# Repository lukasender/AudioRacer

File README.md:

AudioRacer
=========
University Project

### Videos

[YouTube: Wireless car control via zigbee](http://www.youtube.com/watch?v=whj3E_e5Ng8) (First test run)

[YouTube: AudioRacer](http://www.youtube.com/watch?v=RgHPVbPUozI)

### Information
C code for the ZigBee control software is not hosted on github due to the Texas Instruments Inc. Library license model.

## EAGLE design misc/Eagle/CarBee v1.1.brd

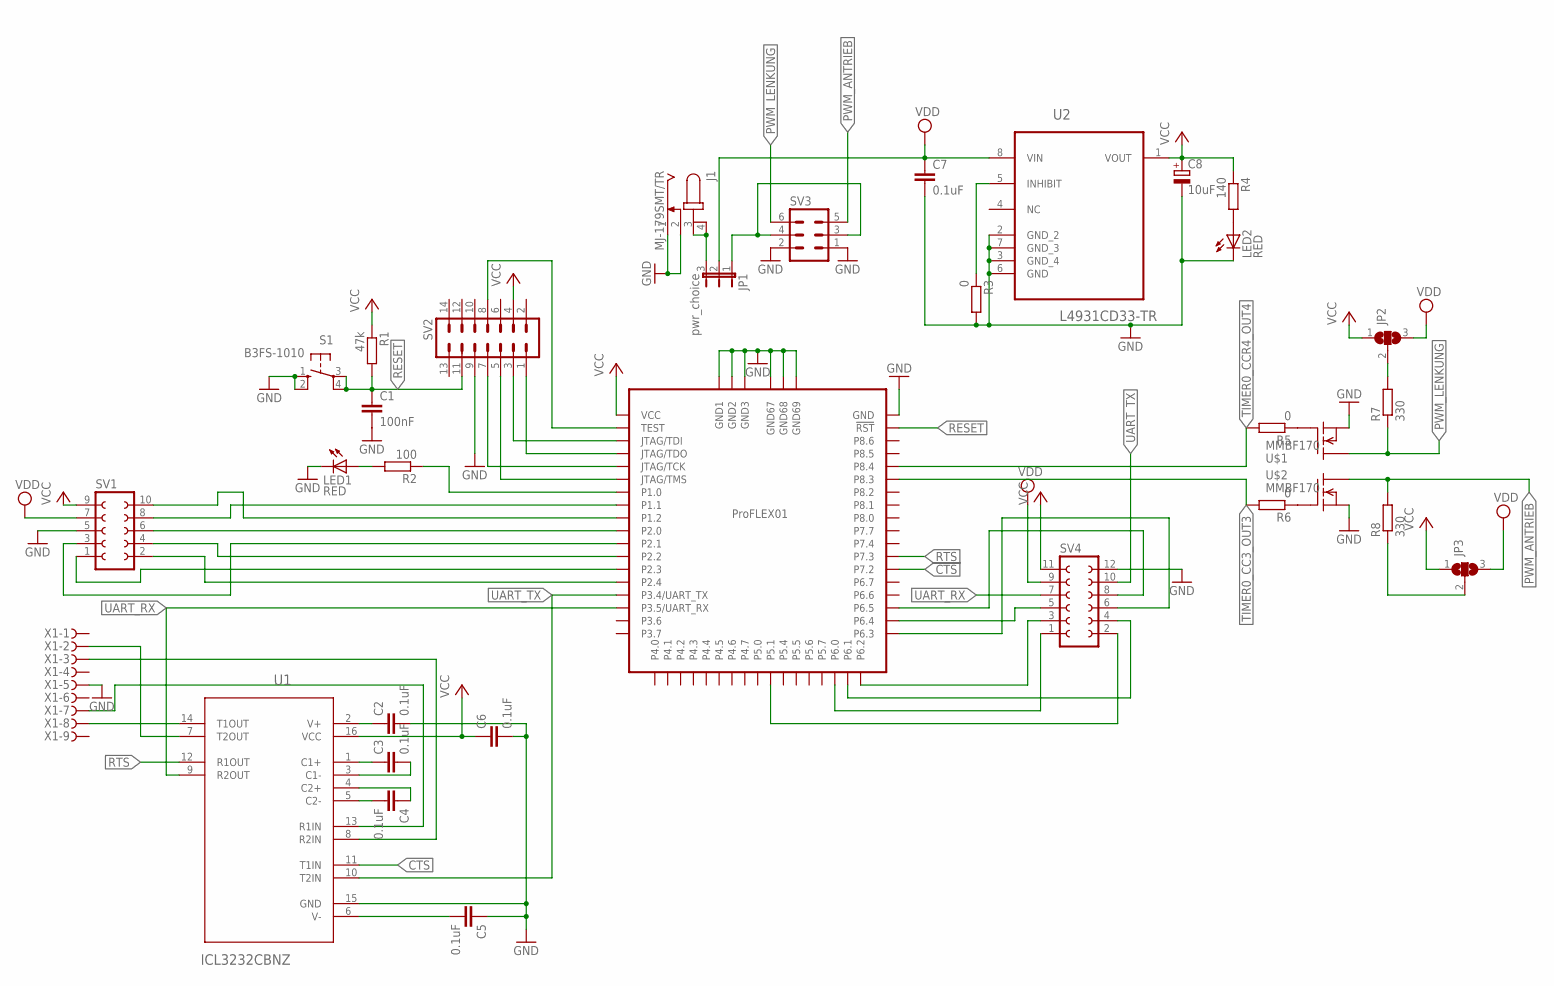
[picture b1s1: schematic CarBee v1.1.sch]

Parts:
C1: 100nF; C0603; MPN 0306ZC104KAT2A
C2, C4, C5, C7: 0.1uF; C0603
C3, C6: 0.1uF; C0603; MPN 0306ZC104KAT2A
C8: 10uF; PANASONIC_B
J1: MJ-179SMT/TR; MJ-179SMT
JP1: pwr_choice; JP2
JP2, JP3: SJ2W; SJ_2
LED1, LED2: RED; CHIP-LED0603
MOD1: PROFLEX01; MODFLEX01
R1: 47k; R0603
R2: 100; R0603
R3, R5, R6: 0; R0603
R4: 140; R0603
R7, R8: 330; R0603
S1: B3FS-1010
SV1: FE05-2
SV2: ML14
SV3: MA03-2
SV4: FE06-2
U1: ICL3232CBNZ; SOIC127P600X175-16N
U2: L4931CD33-TR; SOIC127P600X175-8N
U$1, U$2: MMBF170; SOT23
X1: F09HPS; F09HP

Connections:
CTS: MOD1.P$37 (P7.2), U1.11 (T1IN)
GND: C1.2, C2.2, C5.1, C6.2, C7.2, C8.-, J1.1, J1.2, LED1.C, LED2.C, MOD1.P$1 (GND1), MOD1.P$2 (GND2), MOD1.P$3 (GND3), MOD1.P$44 (GND), MOD1.P$67 (GND67), MOD1.P$68 (GND68), MOD1.P$69 (GND69), R3.2, S1.1 (S), S1.2 (S1), SV1.5, SV2.9, SV3.1, SV3.2, SV4.12, U1.15 (GND), U2.2 (GND_2), U2.3 (GND_4), U2.6 (GND), U2.7 (GND_3), U$1.2 (S), U$2.2 (S), X1.5
unnamed: MOD1.P$13 (TEST), SV2.8
unnamed: LED2.A, R4.2
unnamed: MOD1.P$55 (P2.4), SV1.2
unnamed: MOD1.P$21 (P6.4), SV4.5
unnamed: MOD1.P$52 (P2.1), SV1.3
unnamed: U1.8 (R2IN), X1.3
unnamed: C3.1, U1.1 (C1+)
unnamed: C3.2, U1.3 (C1-)
unnamed: MOD1.P$16 (P5.1), SV4.2
unnamed: C4.1, U1.4 (C2+)
unnamed: C2.1, U1.2 (V+)
unnamed: C5.2, U1.6 (V-)
unnamed: J1.3, J1.4, JP1.3
unnamed: JP2.2, R7.2
unnamed: MOD1.P$51 (P2.0), SV1.6
unnamed: MOD1.P$19 (P6.2), SV4.3
unnamed: MOD1.P$18 (P6.1), SV4.4
unnamed: MOD1.P$20 (P6.3), SV4.6
unnamed: MOD1.P$22 (P6.5), SV4.8
unnamed: MOD1.P$17 (P6.0), SV4.1
unnamed: MOD1.P$49 (P1.0), R2.1
unnamed: LED1.A, R2.2
unnamed: MOD1.P$53 (P2.2), SV1.4
unnamed: U1.14 (T1OUT), X1.8
unnamed: MOD1.P$50 (P1.1), SV1.8
unnamed: U1.13 (R1IN), X1.7
unnamed: U1.7 (T2OUT), X1.2
unnamed: MOD1.P$47 (P1.2), SV1.10
unnamed: JP1.1, SV3.3, SV3.4
unnamed: R5.1, U$1.1 (G)
unnamed: R6.1, U$2.1 (G)
unnamed: R3.1, U2.5 (INHIBIT)
unnamed: MOD1.P$54 (P2.3), SV1.1
unnamed: MOD1.P$12 (JTAG/TDO), SV2.1
unnamed: MOD1.P$10 (JTAG/TDI), SV2.3
unnamed: MOD1.P$9 (JTAG/TMS), SV2.5
unnamed: MOD1.P$11 (JTAG/TCK), SV2.7
unnamed: C4.2, U1.5 (C2-)
unnamed: JP3.2, R8.1
PWM_ANTRIEB: R8.2, SV3.5, U$2.3 (D)
PWM_LENKUNG: R7.1, SV3.6, U$1.3 (D)
RESET: C1.1, MOD1.P$14 (!RST), R1.2, S1.3, S1.4 (P1), SV2.11
RTS: MOD1.P$38 (P7.3), U1.12 (R1OUT)
TIMER0_CC3_OUT3: MOD1.P$42 (P8.3), R6.2
TIMER0_CCR4_OUT4: MOD1.P$41 (P8.4), R5.2
UART_RX: MOD1.P$36 (P3.5/UART_RX), SV4.7, U1.9 (R2OUT)
UART_TX: MOD1.P$35 (P3.4/UART_TX), SV4.10, U1.10 (T2IN)
VCC: C6.1, C8.+, JP2.1, JP3.1, MOD1.P$26 (VCC), R1.1, R4.1, SV1.9, SV2.4, SV4.11, U1.16 (VCC), U2.1 (VOUT)
VDD: C7.1, JP1.2, JP2.3, JP3.3, SV1.7, SV4.9, U2.8 (VIN)

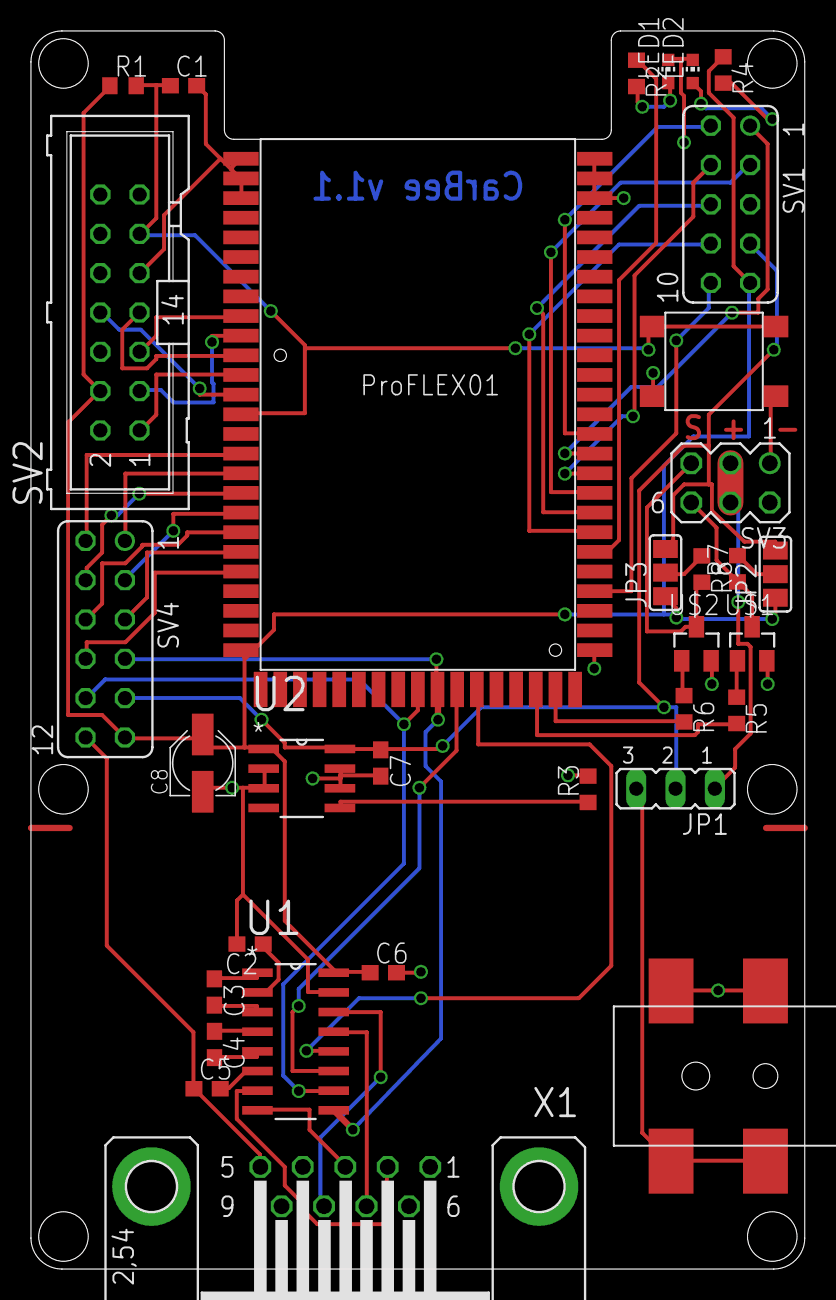
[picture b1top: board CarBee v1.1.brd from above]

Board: 2 copper layers, 50.0 x 80.0 mm, 33 parts (0 on the bottom side), 51 nets.

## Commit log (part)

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2013-09-28 Changed project name
2013-09-28 created a draft API for camera <-> server
2013-10-10 Initial project configuration
2013-10-17 Mover AudioRacer-Communication to AudioRacer-WorldCommunication Added Interfaces diagram
2013-10-17 log4j-1.2.17 and slf4j-1.7.5 added to global "AudioRacer" and tested in "AudioRacer-Server"
2013-10-17 First dummy implementation. Player can choose a name. The name will be stored automatically. If a name has been stored already, it will use the stored name.
2013-10-17 Added basic 'view available games/servers' list view
2013-10-18 Added UI for world simulator including adding all necessary elements: * MapComponent * Core project containing Model * ...
2013-10-18 Added example for Kryonet client / server
    Changing paradigma of Manager/Client:
    * Now each Client has a own Manager
    * The manager knows his client
    * Should work for simulators and Kryonet
2013-10-21 Work on networking and server internals
2013-10-23 null safe Car. It'll throw an IllegalArgumentException when 'BufferedImage image' is not provided.
2013-10-24 introduced simulatedplayerclient and model.player server.dao.player now extends from model.player
2013-10-25 Some minor changes in server and player project Some documentation added
2013-10-30 Added project AudioRacer-Core to AutioRacer-WorldSimulator
2013-10-30 Some first basic implementations: - WorldSim takes care of initialization of the map - Mapped buttons and text fields
    Introduced Initializer which should take care of the initialization process
2013-10-30 Managed imports after merge. 'master' does not know about the moved 'Direction' and 'Position' classes.
2013-10-30 Add car: Set car to different position than the previously added car.
2013-10-31 ICarManager interface changes
2013-11-03 Server documentation added
2013-11-05 backup commit
2013-11-07 prepare for merge and refactoring
2013-11-07 fixed imports
2013-11-07 Server-Dokumentation 5) changed, removed open issue gameStart
2013-11-09 renamed 'Initializer' to 'SimulationController'
2013-11-09 cleanup
2013-11-09 established 'ICamera' and 'ICarClientManager' connections
2013-11-09 fixed typo
2013-11-09 provide map config to server
2013-11-09 better exception handling: will now show a message if a car couldn't be added. got rid of unnecessary methods.
2013-11-09 Better 'map-handling'. Now provides new map config to server on update, not just initialization.
2013-11-09 added CarListener
2013-11-09 Player-Server communication changed - not using RemoteObjects anymore
2013-11-12 player "connect"; camera "carDetected"; player "updateFreeCars" are working as expected, current implementation without RemoteObjects of Kryonet
2013-11-13 Revert previously deleted CarClientManager
2013-11-13 deleted unnecessary Proxy.
2013-11-13 Message are now used to notify the server about newly added cars,...
2013-11-13 - Fixed CarClientListener: use new messaging method - UpdateCarMessage: fixed typo
2013-11-13 Added 'AllCarsDetected' functionality
2013-11-14 Removed TMP File of Server Documentation Added TMP Office files to gitignore
2013-11-14 kryonetregister new message classes
2013-11-15 broadcastFreeCars handle ConcurrentModificationException ... don't send message in that case
2013-11-15 refactor commit Replaced "connet" by "setPlayerName". Set the player name, this is what happens here.
2013-11-20 Comments
2013-11-20 calculated new position
2013-11-20 game moderation refactored and player "disconnect" implemented
2013-11-20 UpdateCarMessage knows his message id, fixed
2013-11-27 removed _gameModerator.startModerating() and refactored slightly
2013-11-27 working on Zigbee (CarClientManager) <-> Server <-> world (car detected by camera) integration.
    Current issue to solve during debugging of WorldSimulator and Server implemenation: CarClientManager is instantiated twice and singleton is not shared among the two applications.
2013-12-05 Start server on WorldSim startup
2013-12-05 different default map size
2013-12-05 improved 'add car' positioning in world simulator
2013-12-05 added project and lib dependencies
2013-12-05 improved logging
2013-12-05 updated kyronet from 2.18 to 2.21
2013-12-06 trying to discover other hosts
2013-12-07 Fast and dirty implementation of a pivot gui for the player simulator. Doesn't handle any kind of problems or exceptions (e.g. connection gone, ...)
    Still some features are missing, like game status and scoreboard.
2013-12-07 First draft implementation to discover hosts.
2013-12-11 changed java version to java 6
2013-12-12 host discovering on android: - now using the same source base as in PlayerSimulator. - using my own AndroidThreadProxy which requires a IThreadProxy. - got rid of old implementation.
2013-12-12 when stopping host discovering, the list of known server will be cleared now.
2013-12-12 Bug fix, caused by CarControlComponent.java behavior -> the components starts sending UpdateVelocityMessages instantly. This behavior is totally valid but caused zigbee-pairing to fail. In current im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
2013-12-12 android: removed network.ClientManager
2013-12-12 android: added basic SelectCarActivity as ListActivity
2013-12-12 cpu usage of WorldSimulator reduced
2013-12-12 playerclient: got rid of 'Car'. was replaced by the car id. The 'Car' used some Java SE stuff (e.g. awt) which is not available on Android.
2013-12-12 android: implemented Connect to host.
2013-12-12 android: better logging
2013-12-12 added missing enumeration. formatting. alphabetical ordering.
2013-12-12 play sound button implementation
2013-12-12 something
2013-12-12 added Vector as utility class for vector calculations
2013-12-12 android: make tasks even more abstract
2013-12-12 android: added non working select car activity
2013-12-18 Start activity has now button play sound
2013-12-18 changed compiler setting from java 1.7 to java 1.6 because of android issues
2013-12-19 server side checkpoint generation
2013-12-19 android: fixed 'select car'.
2014-01-02 Prepared MapComponent to draw checkpoints
2014-01-02 Fix for last commit.
2014-01-03 Fix 2 for last commit. CarDetectedMessage now contains initial position and direction.
2014-01-03 Server side car movement monitoring via GUI. Pass "--gui=false" to server application if you don't want the GUI-monitor on server side. A strange behavior occured during development. During WorldSimu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
2014-01-03 Server side checkpoint monitoring via GUI.
2014-01-03 android: removed 'play sound' button from start activity.
2014-01-03 bugfix: type of carId has changed from int to byte.
2014-01-03 android: when selecting a car, the app will switch to the 'play game' activity.
2014-01-04 Added trim to ICarClient Implemented trim in SerialInterface
2014-01-04 android: - added basic layouts: 'choose control mode' and 'standard controls'
2014-01-04 android: set 'playerReady'. - also, change to the chosen control mode _after_ the player was set to ready.
2014-01-05 android: - added new control layer for 'Motion Sensors' - dummy implementation for displaying current 'motion position' - added new base class for the different threads 'ControlThread'
2014-01-05 android: drawing point on screen with actual motion sensor values (but it still does not seem to work quite well).
2014-01-05 android: start/stop threads like oracle describes it: http://docs.oracle.com/javase/1.5.0/docs/guide/misc/threadPrimitiveDeprecation.html
2014-01-06 android: hardening 'PlayGameActivity': - disable controls when a player leaves/pauses the app (e.g. by pressing the home button). - enable the controls again when the player resumes.
2014-01-06 android: hardening AsynTask
2014-01-06 android: renaming the activities. cleanup unused @strings
2014-01-08 android: improved logging
2014-01-08 android: added missing 'set view invisible' at activity start up
2014-01-08 android: cleanup. fixed: set return value to 'true' for OnTouchListener
2014-01-08 android: hardening: set speed and direction to 0 when reseting.
2014-01-08 car to checkpoint relative distance calculation
2014-01-09 SerialInterface: fixed order of update velocity command
2014-01-09 android: call the actual trim and send a message to the server.
2014-01-09 improved logging in GameModerator
2014-01-09 updated README: added YouTube link
2014-01-09 First car control test run succeeded with this code: http://www.youtube.com/watch?v=whj3E_e5Ng8
2014-01-10 Introduced Player on server side who inherits from core.model.player. Because server uses core.model.car as the others we introduced generic Player-Type in Car.java.
2014-01-10 Direction to next checkpoint send from server to player. Works in simulator as expected.
2014-01-16 Added udp flow control to UpdateVelocityMessage
2014-01-16 commit again
2014-01-16 fixing possible underflows in 2573af7 @see PlayerConnection.isValidUpdateVelocityMessage
2014-01-16 again
2014-01-16 android: improved handling. max speed is now reached in 250ms. braking will now actually make a difference.
2014-01-16 broadcast initial game state of all players on game start to all players
2014-01-16 android: ControlThread takes care of the SoundPlayer2D. - it creates and adds a listener to get the next checkpoint position. - starts and stops the sound player.
2014-01-16 tell new player about all other players currently connected to cars
2014-01-16 Added API for camera <--> GUI communications
2014-01-16 server sends end game to the clients on game end
2014-01-18 fix build error introduced in 91aca37
2014-01-18 handle zig bee network-problem on server side - pause game on at least one pending connection
2014-01-19 Camera: implemented game area selection and map configuration
2014-01-19 Camera: implemented map/car listener, all cars detected + communications
2014-01-21 work in progress
2014-01-22 Fixed sound direction Fixed camera classpath Added logging to PlayerClient to find the bug when no cars are shown in the android application
2014-01-23 android: refactored PlayGameActivity: moved threads/utils to separate package.
2014-01-23 android: bugfix
2014-01-23 Added joystick controls
2014-01-23 player reconnect implemented (server - player simulator), implementation currently contains two bugs pointed out with TODO
2014-01-23 android: move JoystickControlThread to a separate class to fit refactoring
2014-01-23 bug "simulator update position doesn't work aynmore after reconnect" introduced in last commit resolved
2014-01-23 poygon recognition
2014-01-23 android: updated fullscreen theme
2014-01-25 Camera UI: added sliders for color filtering
2014-01-25 Moved dummy car images to UI project
2014-01-25 changed from chape to color matching
2014-01-25 repaint on setImage()
2014-01-25 commented null check in constructor
2014-01-25 Added Wrapper class for model.Car on OpenCVCamera
2014-01-25 display only next checkpoint of each car in server monitoring gui
2014-01-25 Camera: added calibration
2014-01-25 introduced little "hidden" hack to test concurrency handling on server with two instances of player simulator on one machine
2014-01-26 After game round completed, "Ready" can be sent to announce readiness for next round. Implemented and tested with plr-simulator/server implementation.
2014-01-26 Added scoreboard to the server view
2014-01-26 Camera UI: added HUE value detection when clicking on the camera image during car configuration
2014-01-26 WorldSimulator: removed dead code
2014-01-26 Disconnect Player from Car implemented.
    - after game over (Client has to send PlayerMessage.DISCONNECT)
    notice: otherwise client has to send PlayerMessage.SET_READY to announce readiness for next game round
    - on network connection abort (client-server) and timeout exceeded (currently 15 seconds) Car is also disconnected from Player
    notices:
    -> should work at any time
    -> No matter what caused the disconnect - Car will be available again to all Players after timeout exceeded (free cars message)
2014-01-26 Refactored UpdateGameStateMessage so that it contains the PlayerId instead of the CarId
2014-01-26 implemented OnGameEnd
2014-01-26 calibration data for industrial camera
2014-01-27 configureCar button now detects car and calculates direction and position of configuredCar
2014-01-28 implemented directionConfigured, carConfigured and AllCarsDetected on Camera
2014-01-28 bug fix: game doent't start when "car detected" is called after all players are ready
2014-01-28 server monitoring: mark free cars, display player names and reconnecting states
2014-01-29 Fixed a lot of the AsyncTask problems
2014-01-29 removed awt classes from core project
2014-01-29 Android: Changed max distance for AUI to map size during presentation
2014-01-29 send UpdateCarMessage in player simulator via udp
2014-01-29 Andriod: added vibration when a checkpoint is reached All: some bug fixes
2014-01-29 wip done should be final version of camera
2014-01-29 server monitoring, display player name in current checkpoint
2014-01-29 Added eagle files
2014-01-29 finished implementation of game stats list
2014-01-29 directionConfigured now works properly
2014-01-29 Camera: storing and loading of game area configuration
2014-02-07 Bug fix CameraSplitPane
